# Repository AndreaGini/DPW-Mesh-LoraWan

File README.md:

# DPW-Mesh-LoraWan

Instruction and How-To coming soon

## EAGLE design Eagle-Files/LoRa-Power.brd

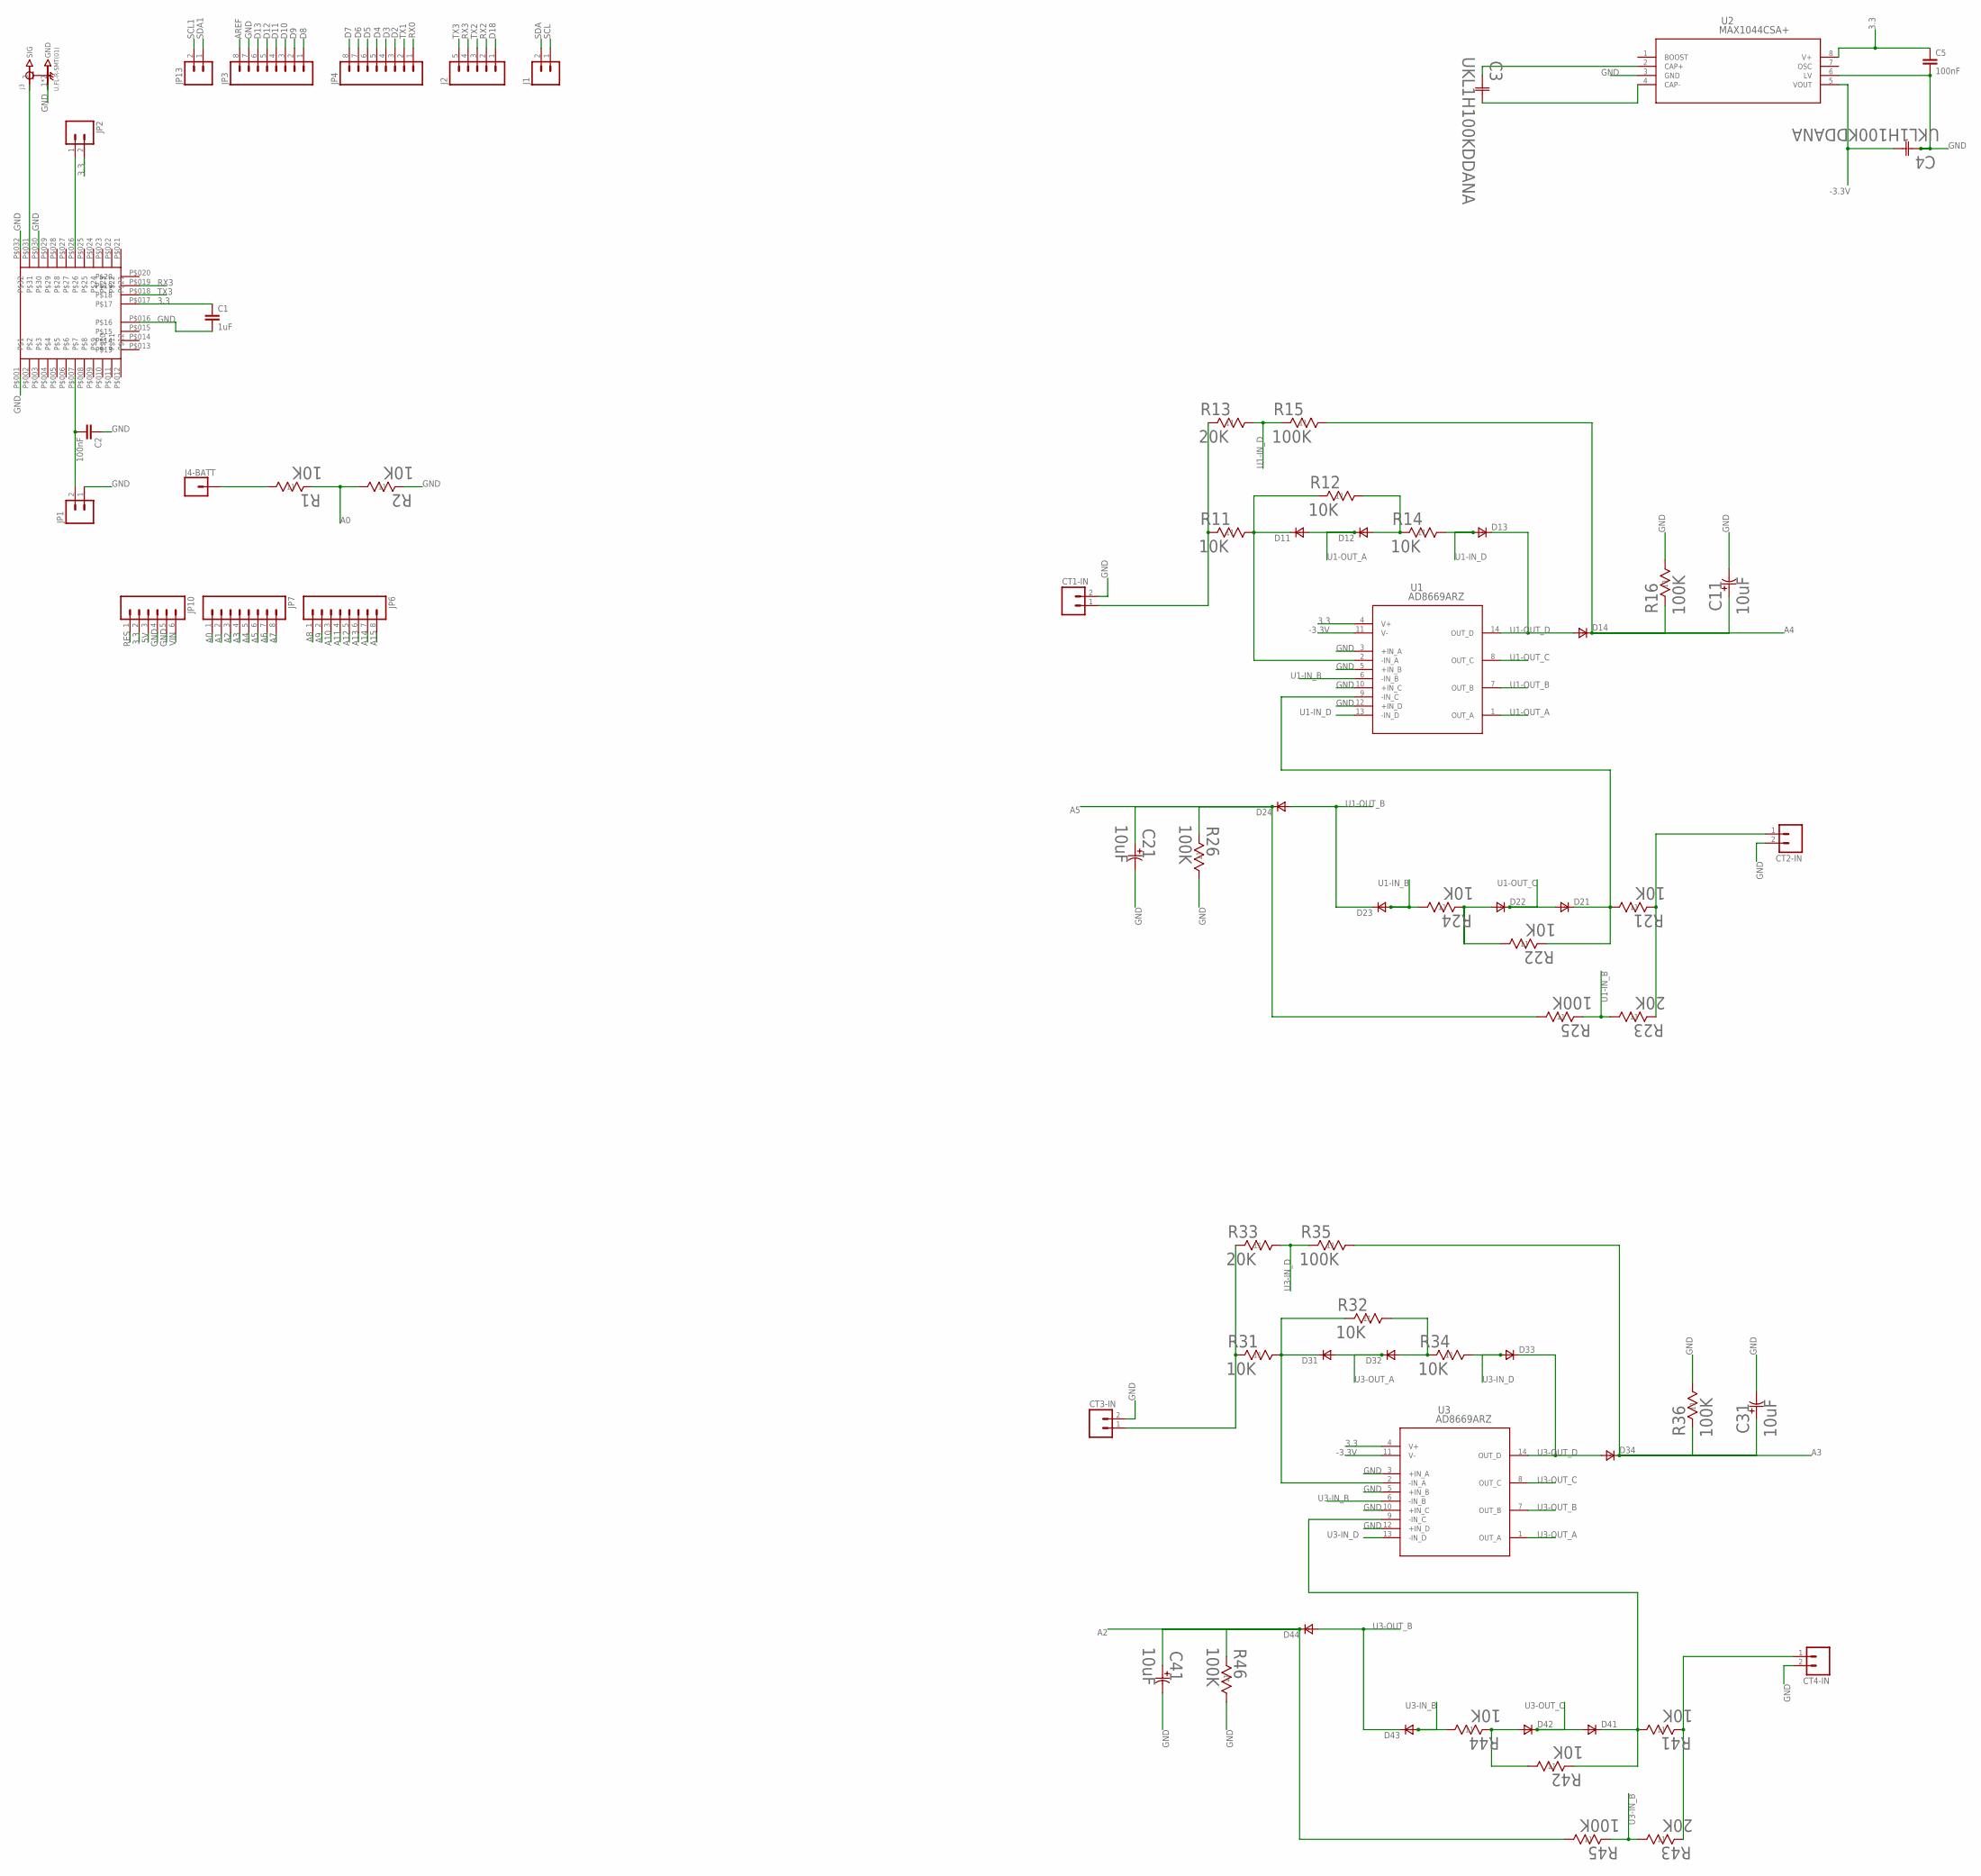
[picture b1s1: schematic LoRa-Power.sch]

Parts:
C1: 1uF; C0603K
C2: 100nF; C0603K
C3, C4: UKL1H100KDDANA; U1-E
C5: 100nF; C1206K
C11, C21, C31, C41: 10uF; C1206
CT1-IN, CT2-IN, CT3-IN, CT4-IN: M02LOCK; 1X02_LOCK
D11, D12, D13, D14, D21, D22, D23, D24, D31, D32, D33, D34, D41, D42, D43, D44: DSOT23; SOT-23
IM1: IM880B
J1: M02LOCK; 1X02_LOCK
J2: M05LOCK; 1X05_LOCK
J3: U.FL-R-SMT(01); HRS_U.FL-R-SMT(01)
J4-BATT: CONN_01; 1X01
JP1, JP2, JP13: M02LOCK; 1X02_LOCK
JP3, JP4, JP6, JP7: M08LOCK; 1X08_LOCK
JP10: M06LOCK; 1X06_LOCK
R1, R2, R11, R12, R14, R21, R22, R24, R31, R32, R34, R41, R42, R44: 10K; 1206
R13, R23, R33, R43: 20K; 1206
R15, R16, R25, R26, R35, R36, R45, R46: 100K; 1206
U1, U3: AD8669ARZ; R_14
U2: MAX1044CSA+; 21-0041B_8

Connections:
3.3: C1.1, C5.1, IM1.P$017, JP2.2, JP10.2, U1.4 (V+), U2.8 (V+), U3.4 (V+)
5V: JP10.3
-3.3V: C4.2 (22), U1.11 (V-), U2.5 (VOUT), U3.11 (V-)
A0: JP7.1, R1.1 (11), R2.2 (22)
A1: JP7.2
A2: C41.1 (11), D44.1 (C), JP7.3, R45.2 (22), R46.1 (11)
A3: C31.1 (11), D34.1 (C), JP7.4, R35.2 (22), R36.1 (11)
A4: C11.1 (11), D14.1 (C), JP7.5, R15.2 (22), R16.1 (11)
A5: C21.1 (11), D24.1 (C), JP7.6, R25.2 (22), R26.1 (11)
A6: JP7.7
A7: JP7.8
A8: JP6.1
A9: JP6.2
A10: JP6.3
A11: JP6.4
A12: JP6.5
A13: JP6.6
A14: JP6.7
A15: JP6.8
AREF: JP3.8
D2: JP4.3
D3: JP4.4
D4: JP4.5
D5: JP4.6
D6: JP4.7
D7: JP4.8
D8: JP3.1
D9: JP3.2
D10: JP3.3
D11: JP3.4
D12: JP3.5
D13: JP3.6
D18: J2.1
GND: C1.2, C2.1, C4.1 (11), C5.2, C11.2 (22), C21.2 (22), C31.2 (22), C41.2 (22), CT1-IN.2, CT2-IN.2, CT3-IN.2, CT4-IN.2, IM1.P$001, IM1.P$016, IM1.P$030, IM1.P$032, J3.1 (GND), J3.2 (GND), JP1.1, JP3.7, JP10.4, JP10.5, R2.1 (11), R16.2 (22), R26.2 (22), R36.2 (22), R46.2 (22), U1.3 (+IN_A), U1.5 (+IN_B), U1.10 (+IN_C), U1.12 (+IN_D), U2.3 (GND), U2.6 (LV), U3.3 (+IN_A), U3.5 (+IN_B), U3.10 (+IN_C), U3.12 (+IN_D)
unnamed: IM1.P$031, J3.3 (SIG)
unnamed: C2.2, IM1.P$007, JP1.2
unnamed: IM1.P$026, JP2.1
unnamed: C3.1 (11), U2.2 (CAP+)
unnamed: C3.2 (22), U2.4 (CAP-)
unnamed: CT1-IN.1, R11.1 (11), R13.1 (11)
unnamed: D11.1 (C), R11.2 (22), R12.1 (11), U1.2 (-IN_A)
unnamed: D12.3 (A), R12.2 (22), R14.1 (11)
unnamed: CT2-IN.1, R21.1 (11), R23.1 (11)
unnamed: D21.1 (C), R21.2 (22), R22.1 (11), U1.9 (-IN_C)
unnamed: D22.3 (A), R22.2 (22), R24.1 (11)
unnamed: CT3-IN.1, R31.1 (11), R33.1 (11)
unnamed: D31.1 (C), R31.2 (22), R32.1 (11), U3.2 (-IN_A)
unnamed: D32.3 (A), R32.2 (22), R34.1 (11)
unnamed: CT4-IN.1, R41.1 (11), R43.1 (11)
unnamed: D41.1 (C), R41.2 (22), R42.1 (11), U3.9 (-IN_C)
unnamed: D42.3 (A), R42.2 (22), R44.1 (11)
unnamed: J4-BATT.1, R1.2 (22)
RES: JP10.1
RX0: JP4.1
RX2: J2.2
RX3: IM1.P$019, J2.4
SCL: J1.1
SCL1: JP13.2
SDA: J1.2
SDA1: JP13.1
TX1: JP4.2
TX2: J2.3
TX3: IM1.P$018, J2.5
U1-IN_B: D23.3 (A), R23.2 (22), R24.2 (22), R25.1 (11), U1.6 (-IN_B)
U1-IN_D: D13.3 (A), R13.2 (22), R14.2 (22), R15.1 (11), U1.13 (-IN_D)
U1-OUT_A: D11.3 (A), D12.1 (C), U1.1 (OUT_A)
U1-OUT_B: D23.1 (C), D24.3 (A), U1.7 (OUT_B)
U1-OUT_C: D21.3 (A), D22.1 (C), U1.8 (OUT_C)
U1-OUT_D: D13.1 (C), D14.3 (A), U1.14 (OUT_D)
U3-IN_B: D43.3 (A), R43.2 (22), R44.2 (22), R45.1 (11), U3.6 (-IN_B)
U3-IN_D: D33.3 (A), R33.2 (22), R34.2 (22), R35.1 (11), U3.13 (-IN_D)
U3-OUT_A: D31.3 (A), D32.1 (C), U3.1 (OUT_A)
U3-OUT_B: D43.1 (C), D44.3 (A), U3.7 (OUT_B)
U3-OUT_C: D41.3 (A), D42.1 (C), U3.8 (OUT_C)
U3-OUT_D: D33.1 (C), D34.3 (A), U3.14 (OUT_D)
VIN: JP10.6

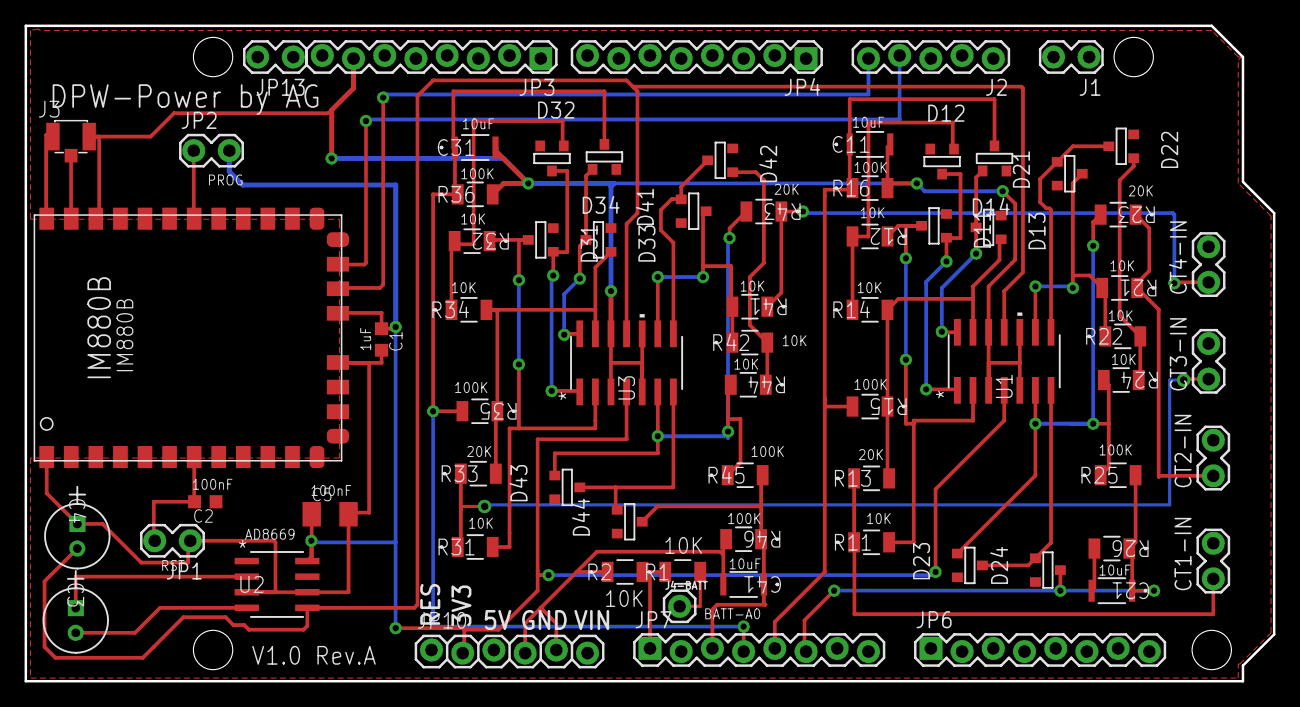
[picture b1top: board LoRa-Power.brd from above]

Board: 2 copper layers, 101.6 x 53.3 mm, 71 parts (0 on the bottom side), 40 nets.

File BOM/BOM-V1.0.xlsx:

Description | SKU | Provider
SMA-antenna for iC880A-SPI | 404811 | http://webshop.imst.de
iC880A-SPI – LoRaWAN Concentrator 868MHz | 404802 | http://webshop.imst.de
Pigtail for iC880A-SPI | 404812 | http://webshop.imst.de
iM880B-L LoRaWAN - Long Range Radio Module | 404791 | http://webshop.imst.de
iC880A LoRaWAN Gateway Backplane | N.A. | https://shop.coredump.ch/
XH-SCT-1250 SPLIT CORE Sensor | XH-SCT-1250-600 | http://www.rogowski-coil-sensor.com
SAMSUNG 18650 3.7v Li-IoN 2600mAh | 788-7261 | http://es.rs-online.com
PCB HOLDER BATTERY 1CELL 18650 | BH-18650-W-ND | https://www.digikey.es
Electrolytic Capacitor 10µF | UKL1H100KDDANA-ND | https://www.digikey.es
Ceramic Capacitor 100nF | 587-1147-1-ND | https://www.digikey.es
Ceramic Capacitor 10µF | 399-9310-1-ND | https://www.digikey.es
Switching Diode 1N4148 | MMBD914LT3GOSCT-ND | https://www.digikey.es
Resistor 10kΩ | P10KBCCT-ND | https://www.digikey.es
Resistor 20kΩ | P20KBCCT-ND | https://www.digikey.es
Resistor 100kΩ | P100KBCCT-ND | https://www.digikey.es
MAX1044 | MAX1044CSA+-ND | https://www.digikey.es
AD8669 | AD8669ARZ-ND | https://www.digikey.es
Screw terminal - 2 pins | A97996-ND | https://www.digikey.es
Arduino due | 1050-1049-ND | https://www.digikey.es
U.FL, Ultra Miniature Coaxial Connector | H122041-ND | https://www.digikey.es

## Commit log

2017-09-19 New Commit
    Project Files Update

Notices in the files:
parts and their libraries:
SparkFun-Connectors: Licensing: Creative Commons ShareAlike 4.0 International - https://creativecommons.org/licenses/by-sa/4.0
